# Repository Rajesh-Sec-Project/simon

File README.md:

# simon

------------
Setup
------------

### Step 1

Grab the project's sources using ```git clone https://github.com/Rajesh-Sec-Project/simon.git```.

### Step 2

Build the GUI component, you will need the Qt5 framework properly insstalled alongside with QtMultimedia.
You will also need QtChooser.
Then, type ```cd host && make release```, all should go well and you should see no errors.

### Step 3

Get a drone (and the LED board). Power-on the drone (but don't plut the LEDs board yet).
Connect your computer to the drone's wifi network, then type in ```utils.d/setup.sh```.
Wait some seconds, then plug in the LEDs when requested, the game should start shortly !

------------
Game screenshots
------------

![Main menu]
(https://raw.githubusercontent.com/Rajesh-Sec-Project/simon/master/docs.d/screenshots/main_menu.png)

![High scores hall of fame]
(https://raw.githubusercontent.com/Rajesh-Sec-Project/simon/master/docs.d/screenshots/high_scores.png)

![Settings page]
(https://raw.githubusercontent.com/Rajesh-Sec-Project/simon/master/docs.d/screenshots/settings.png)

------------
Required tools
------------
The project uses the ```make``` build system. It smartly manages the compilation process for the host applications and the cross-compiled applications for the drone.
To build the embedded app, you will need a valid ARM cross-compiler, with its executable in your ```$PATH```.
The host GUI application uses Qt5 and needs its SDK for building.

------------
Build process
------------
When in the root directory, you can run ```make debug``` or ```make release```, depending on your goal. The command will build the drone app, the GUI app and all of their dependencies.
The project contains 2 misc targets, called ```drone-sandbox``` and ```host-sandbox```, which are only present for test purposes. These targets are meant to build an executable, so as no source file are present in their ```src/``` subdirectory, the compilation will fail (stating that no ```main``` function was found). If you want the whole build process to be successful, you will need to add a minimal ```main``` function in the ```drone-sandbox/src``` and ```host-sandbox/src``` directories, for example like this one in a file called ```main.cpp```:

```
int main() {
    return 0;
}
```

If you prefer not to get involved into this, you can only build the individual targets, like ```drone``` or ```host```, just cd into the corresponding directory and run ```make debug``` or ```make release```.

------------
Embedded deployment
------------
If you want to put the application on the drone, run ```cd drone; make push```. This target manages on its own the FTP connection to the drone and the push of the executable.
This assumes that your are on the drone's WiFi network, that its DHCP server has given you an IP and that you can ```ping 192.168.1.1``` without issue.

The ```make push``` command usually takes a few seconds to copy the executable. If it returns immediately, it means that an error occurred (even if none is reported).
If this is happening, it can mean 2 things: either you did not meet the above preconditions, or the ```drone``` command is running (preventing you to overwrite the executable).

Just run the command ```killall -9 program.elf; killall -9 drone``` to terminate the ```drone``` application and turn back in a restartable state. Note that you may want to execute the previous command each time you want to relaunch the ```drone``` application.

The deployment puts the executable in the drone filesystem's ```/data/video/``` directory, and you can run the app by opening a shell on the drone: ```telnet 192.168.1.1```.

------------
Repository structure
------------

Here is a short roadmap of this repository's top-level structure :

* drone         -> The embedded program sources
* drone-sandbox -> An empty playground for embedded programs
* host          -> The host GUI client sources
* host-sandbox  -> An empty playground for host programs
* docs.d        -> Non-source folder for documentation stuff
* gdb.d         -> Script folder for debugging and executable pushing
* hard.d        -> Hardware sources folder
* libs.d        -> Shared libraries (across drone and host) source folder
* mk.d          -> Internal GNU Make scripts for building the project
* utils.d       -> Utilities scripts folder

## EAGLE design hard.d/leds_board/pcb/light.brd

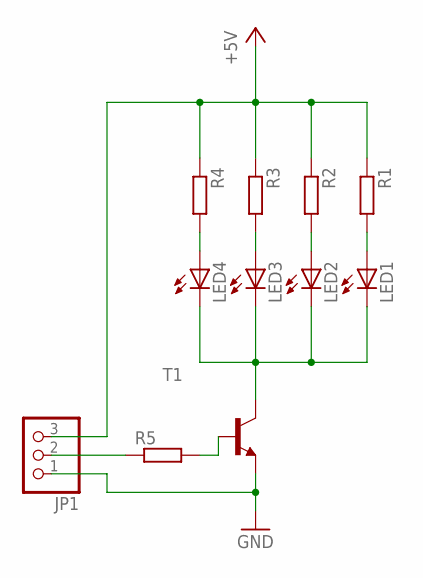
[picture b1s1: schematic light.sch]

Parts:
JP1: PINHD-1X3/90; 1X03/90
LED1, LED2, LED3, LED4: LED3MM
R1, R2, R3, R4, R5: R-EU_0207/10; 0207/10
T1: -NPN-SOT223; SOT223

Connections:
+5V: JP1.3, R1.1, R2.1, R3.1, R4.1
GND: JP1.1, T1.3 (E)
unnamed: LED1.A, R1.2
unnamed: LED2.A, R2.2
unnamed: LED3.A, R3.2
unnamed: LED4.A, R4.2
unnamed: LED1.K (C), LED2.K (C), LED3.K (C), LED4.K (C), T1.4 (C)
unnamed: R5.2, T1.1 (B)
unnamed: JP1.2, R5.1

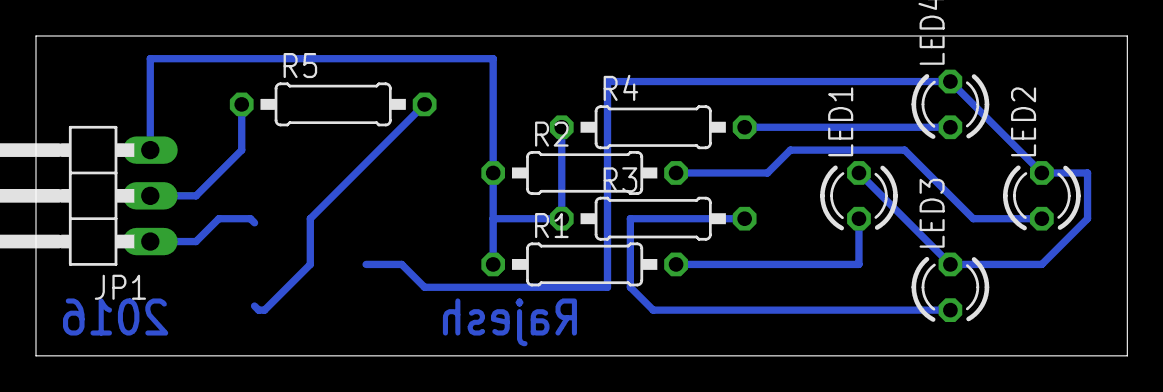
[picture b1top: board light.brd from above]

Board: 2 copper layers, 60.6 x 17.8 mm, 11 parts (1 on the bottom side), 9 nets.

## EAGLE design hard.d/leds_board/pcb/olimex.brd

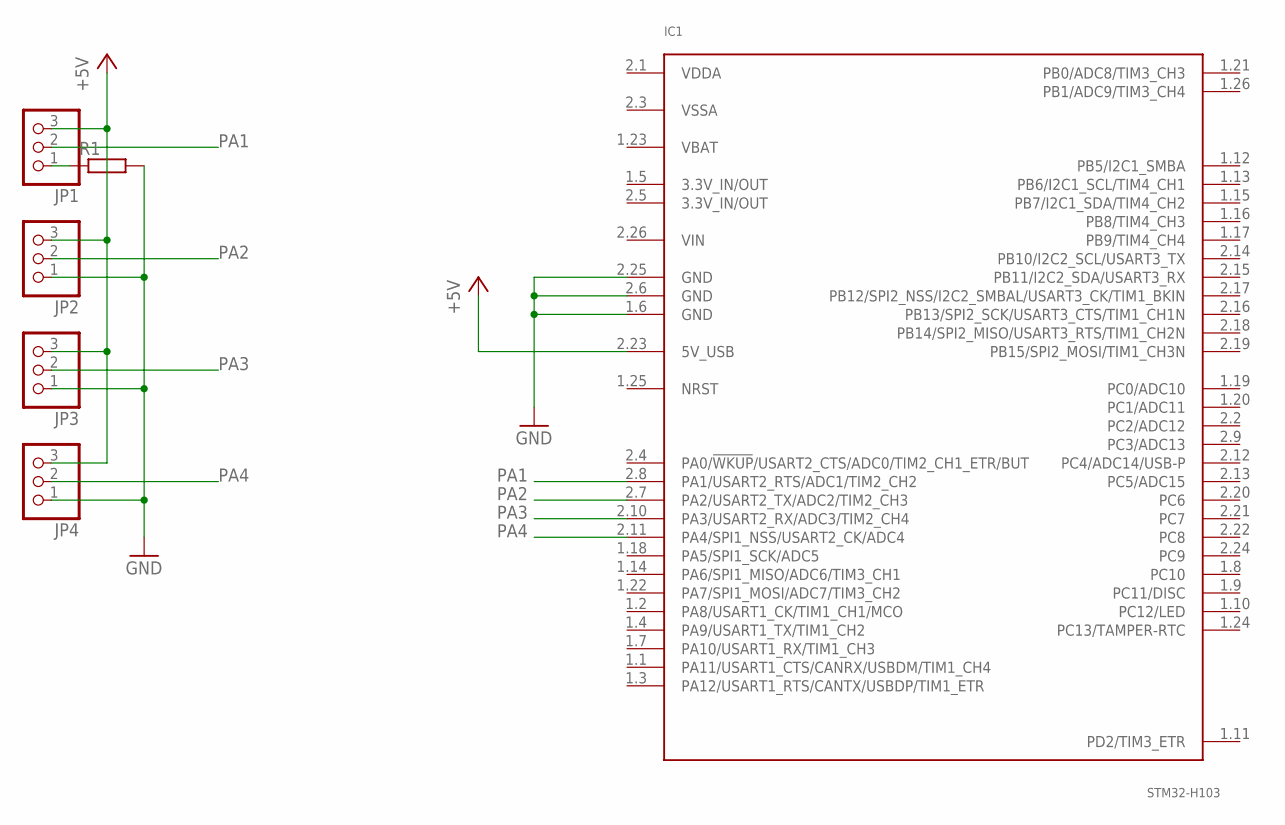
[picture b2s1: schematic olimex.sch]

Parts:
IC1: STM32-H103; OLIMEX_H103_P
JP1, JP2, JP3, JP4: PINHD-1X3/90; 1X03/90
R1: R-EU_0207/10; 0207/10

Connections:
3.3V_IN/OUT: IC1.1.5 (3.3V_IN/OUT), IC1.2.5 (3.3V_IN/OUT)
+5V: IC1.2.23 (5V_USB), JP1.3, JP2.3, JP3.3, JP4.3
GND: IC1.1.6 (GND), IC1.2.6 (GND), IC1.2.25 (GND), JP2.1, JP3.1, JP4.1, R1.2
unnamed: JP1.1, R1.1
PA1: IC1.2.8 (PA1/USART2_RTS/ADC1/TIM2_CH2), JP1.2
PA2: IC1.2.7 (PA2/USART2_TX/ADC2/TIM2_CH3), JP2.2
PA3: IC1.2.10 (PA3/USART2_RX/ADC3/TIM2_CH4), JP3.2
PA4: IC1.2.11 (PA4/SPI1_NSS/USART2_CK/ADC4), JP4.2
VBAT: IC1.1.23 (VBAT)
VDDA: IC1.2.1 (VDDA)
VIN: IC1.2.26 (VIN)
VSSA: IC1.2.3 (VSSA)

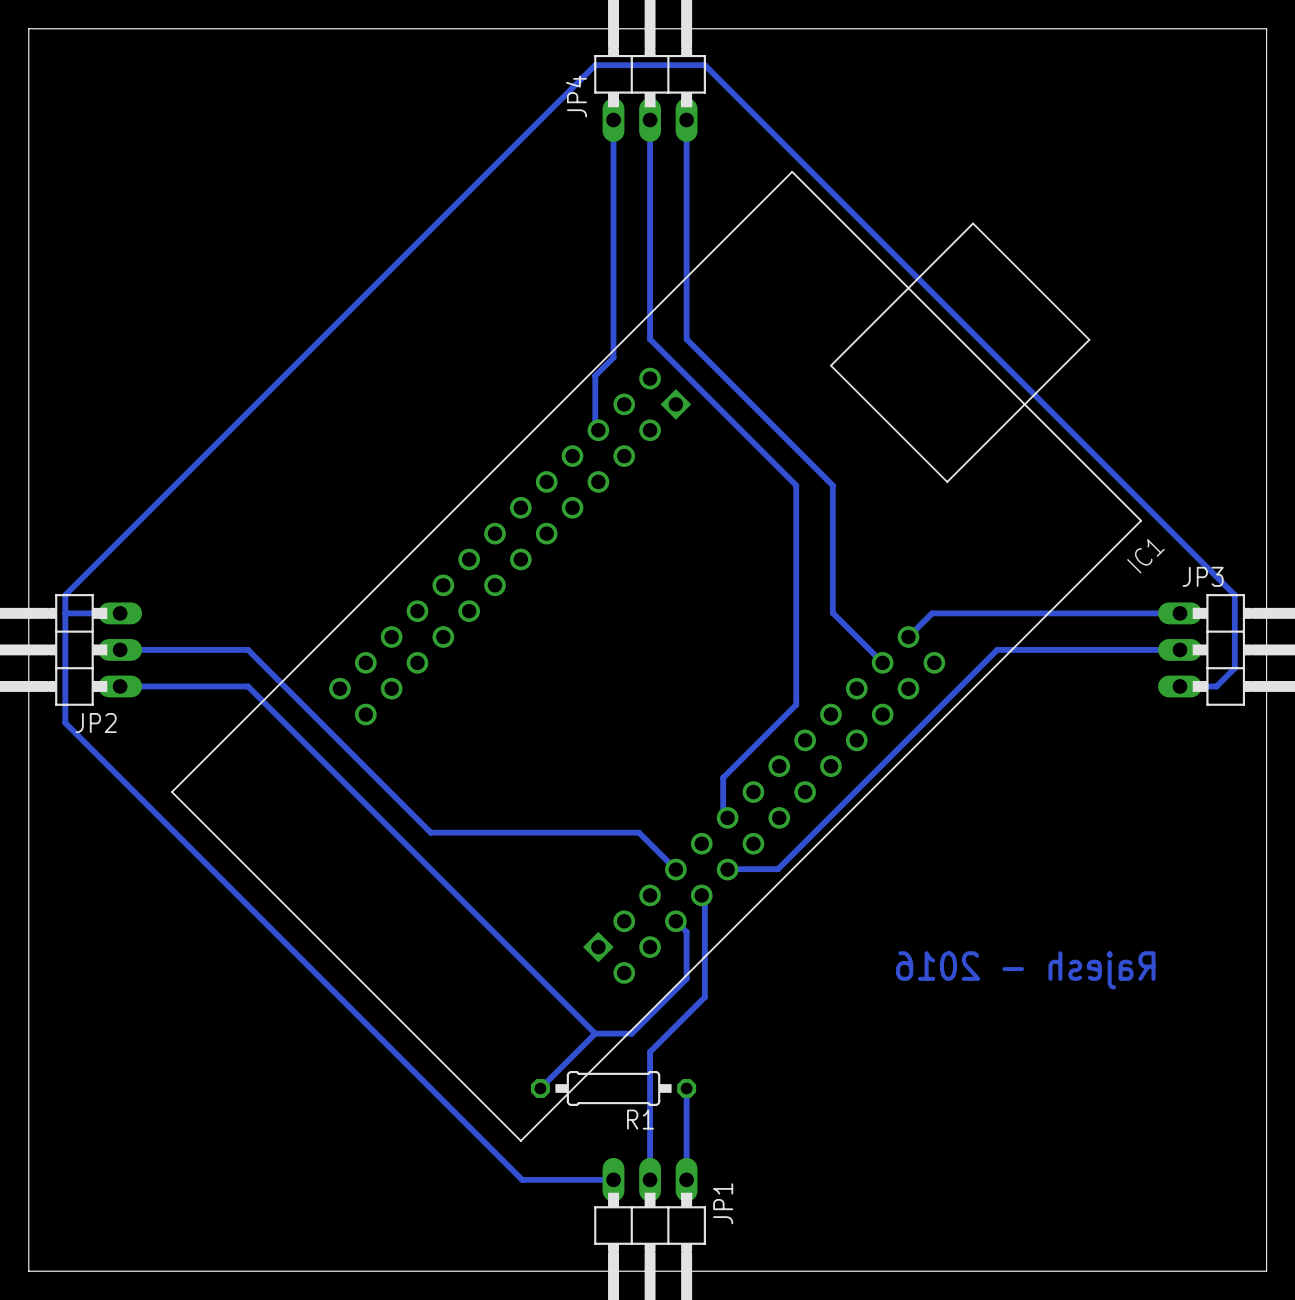
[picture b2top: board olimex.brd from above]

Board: 2 copper layers, 86.0 x 86.3 mm, 6 parts (0 on the bottom side), 8 nets.

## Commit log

2015-11-03 Pushed the build system - Makefile skeletons for embedded and offline source codes - INSTALL.md file for explanation - build system tested good
2015-11-03 Fix typo in INSTALL.md
2015-11-03 Typo fix in INSTALL.md (again !)
2015-11-04 Fixed build system - mk.d/production.mk and mk.d/functions.mk - added static libstdc++ linkage
2015-11-04 Added debug system - see debug/*.sh scripts - can push executable to remote (w/ ftp) - can start/stop debugging session easily - all integrated in the makefiles (push / debug targets)
2015-11-04 Fixed Makefile - two 'debug' rules...
2015-11-04 Modified build & debug system + added shell make target + patched GDB start system (to kill gdbserver before and after session to avoid problems) + updated INSTALL.md
2015-11-05 Fixed push.sh script
2015-11-06 Integrated Qt in the build system - updated INSTALL.md - added help target in Makefiles - added qmake helpers fragments in mk.d/
2015-11-06 Renamed debug/ to gdb.d/ Patched typo in INSTALL.md
2015-11-06 Added a clang-format file, and wrote a small script to automatically format source code
2015-11-06 Configured the Qt project
2015-11-06 Integrated libconf library in project - integrated external dependencies in build system (not yet documented in INSTALL.md)
2015-11-06 Squelette client
2015-11-08 .gitignore
2015-11-08 Formattage
2015-11-08 common
2015-11-08 Added communication protocol bare bones - as an external library in lib.d - added a qemu simulation target (mk.d/qemu.mk)
2015-11-08 Small fixes : - Patched libcomm include guards - Patched external library build system (also override build directory)
2015-11-09 First version of the communication protocol - added BSD socket backends for lcomm::Endpoint - fixed some bugs in lcomm:: - fixed dependency management in build system - fixed root Makefile
2015-11-10 Finishing up libcomm - centralized Packet registerations in a PacketManager static class - added a global lcomm.h header - [ patched .gitignore in libconf submodule ]
2015-11-10 Documented libcomm files - fixed dependency build system (now suports debug/release switch automatically) - added unit tests support for the drone project (make tests-debug or tests-release)
2015-11-10 Fixed .gitignore
2015-11-10 Patched .clang-format file - for compat. with clang 3.5 (very lightweigth) - to bind pointers to types (i didn't touched braces Rémi :) ) - to break initializers in constructors
2015-11-10 Added a host-sandbox project for quick integration tests - fixed project names in */conf.mk to reflect their parent folder names
2015-11-10 Formatted previous commits (sorry for dup commit) - added host-sandbox folder to utils.d/format.sh
2015-11-13 Added notes file plus some at and navdata headers
2015-11-13 Fixed makefiles
2015-11-13 Simplified Endpoints and Socket interactions
2015-11-13 Fixed tests
2015-11-13 Added UI's gamepad bare bones - plus gamepad packet
2015-11-13 More GUI stuff
2015-11-13 drone-sandbox
2015-11-13 libcontrol
2015-11-13 More gamepad stuff
2015-11-13 emma, control
2015-11-13 Fixed Q_OBJECT missing
2015-11-13 Added a general info packet in libcomm
2015-11-13 Added new enums to GamepadPacket (land and take off)
2015-11-13 Game system, take off and landing
2015-11-13 Patched game system (less threads :()
2015-11-13 Formating script is up to date.
2015-11-13 Formatted source code
2015-11-14 Better interface to libcontrol
2015-11-14 Endpoint subscriber is now taken by reference
2015-11-14 Endpoint::write
2015-11-14 Subscriber::notify
2015-11-14 Specified the thread-safety of the Socket::read and Socket::write methods
2015-11-14 Cleaned the ServerSocket class from dynamic allocations
2015-11-14 Finished libcomm trimming
2015-11-14 Removed old code from GameSystem, added -Wall flags to the compiler
2015-11-14 Added override specifier where appropriate
2015-11-14 Formatting
2015-11-16 Fixed regression in makefile: missing static libstdc++ in the drone program
2015-11-16 Turned off AT command logging (logging is now on demand).
2015-11-16 Better logging of user actions in the host's application.
2015-11-16 The embedded app is now easier to terminate.
2015-11-16 Small refactoring of the host app.
2015-11-16 Hardenned the connection between the drone and the host: a lost or nonexisting connection provokes reconnection attempts.
2015-11-19 Added a script to start the game on the drone
2015-11-19 Reducing the per-thread stack sie allows more threads to be spawned; thus the game loop thread has been added again.
2015-11-19 libcontrol has now a blocking connection initialization
2015-11-19 Added an UDP spoofing class in libcomm (for navdata)
2015-11-20 Improved drone control's app launch script
2015-11-20 Removed read threads from ClientSocket and ServerSocket
2015-11-20 Removed unnecessary mutex
2015-11-20 Navdata driver working ! - now using libpcap to sniff traffic initiated by spoofer
2015-11-21 add of Moves and RandomSequence
2015-11-22 Added NavdataController (based on spoofing + sniffing) - not yet tested on drone
2015-11-23 Added final (and working !) navdata controller - changed the main game loop structure (and addex watchdog management) - renamed some file lowercase - fixed the lcontrol lib (watchdog fix, added comma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
2015-11-23 Added tag detection bare bones (conf problems !!) - did some renaming of files
2015-11-23 Oops!
2015-11-24 Small changes to drone/
2015-11-24 Added logging system base (not yet tested on the drone) - added a GameElement class to provide global GameSystem access for logging - added a lcomm::LogPacket class (w/ 4 levels of logging, trace/mes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
2015-11-25 Added log interface + information packets (for the UI to know the drone's state) - fixed a LOT (really, A LOOOT) of bugs in the communication things - /!\ PLEASE DON'T TOUCH IT ANYMORE /!\ - added a 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
2015-11-26 Updated game sequence
2015-11-26 Small changes
2015-11-26 Local logging level
2015-11-26 Preliminary drone position control interface
2015-11-26 Added a clock to the game system
2015-11-27 Removed test values
2015-11-27 TAG DETECTION WORKING YOUHOUUUUUUUU - Added multiconfiguration support
2015-11-27 Fixed the game system's clock wraparound, and fixed the game loop's per-iteration wait
2015-11-27 Added tag detetion support in the GUI
2015-11-27 Minimal log level for the GUI
2015-11-27 Main
2015-11-27 Removed the random sequence's test
2015-11-27 Removed unused NAT documentation
2015-11-28 Added compilation/deployment instructions in the README.md file
2015-11-28 Code that compiles is somewhat better, I guess
2015-11-28 gamepad subscriber + gamesystem add of error recognition
2015-11-28 Previous errors modified
2015-11-28 Added a gamepad to control the drone's position
2015-11-28 position control update
2015-11-28 add print sequence
2015-11-28 change debug game system
2015-11-28 debug gamesystem
2015-11-30 change move recognition
2015-11-30 Removed test files
2015-11-30 Integrated Emma's work
2015-11-30 Better GUI, factorization of some code
2015-11-30 Removed empty sources
2015-11-30 Added a black ring aroung the tag target
2015-11-30 Rename RoundelController
2015-12-01 Removed some warnings related to bad aliasing
2015-12-01 Added sprint 0 and 2's review document
2015-12-01 Added tag position conversion (to cm) - started detection compensation
2015-12-01 Added an explanation about tag detection calibration (in docs.d)
2015-12-03 Position control updated avec control selon altitude
2015-12-03 Added a game GUI
2015-12-03 T53 integrated the game control onto the drone
2015-12-03 T53 integrated the host with the client
2015-12-08 Added user move detection algorithms [T54] - added matlab design script and data - all implemented in tagcontroller.h/cpp
2015-12-08 New update on PID and position control T23
2015-12-08 Bug fix in libcontrol
2015-12-08 More work on the PID
2015-12-11 Tuned euler angles PID Added basic moves eecution
2015-12-12 Removed PID samples from repo
2015-12-12 libcontrol is now thread-safe
2015-12-12 T20 T24 Added a position control thread that executes atomic movements.
2015-12-12 Removed the stop button from the gamepads
2015-12-12 T44 Updated motion algorithm
2015-12-12 add of score counting T40 and score display T41
2015-12-17 Changed files mode, don't know why the x bit was set on them.
2015-12-17 PID tuning
2016-01-04 Added a GUI mock for the game, and attributed roles to the developers.
2016-01-07 interface compile pas
2016-01-07 Updated ViewManager and disconnect from the drone
2016-01-10 score: display and save
2016-01-10 Added LED board schematics and first driver version on drone side
2016-01-11 LEDs board driver OK - added driver module 'cdc-acm.ko' in docs.d - be careful to insmod it at startup
2016-01-12 Fixed UI switching
2016-01-12 GameOver message and overall game integration
2016-01-12 Added sprint review presentations 3 and 4.
2016-01-12 Fixes
2016-01-14 Created a skin for the game - added some fonts - changed layouts - TODO: - display tag position in gameview - fix pause/resume bug - fix score bug
2016-01-18 Integrated LED display to the game - added win/lose animations - added user input feedback through LEDs and GUI
2016-01-18 - fixed main menu at startup
2016-01-18 score marche
2016-01-18 Added a sound manager and contextual music backgrounds.
2016-01-18 Added sound notification packet
2016-01-18 Added a sound notification packet (correction)
2016-01-18 Added sound to Qt ressources file
2016-01-18 Updated music locations
2016-01-18 Added sound effects
2016-01-21 Fixed start message sent to drone + Qt5 issues
2016-01-21 The generated moves sequence should now have a uniform distribution.
2016-01-21 Added delay before starting the game
2016-01-21 Loading screen
2016-01-21 Renamed gameview to GameView
2016-01-21 Added the credits view
2016-01-21 Added a library for the chrono stuff.
2016-01-21 Added settings
2016-01-21 Fixed the score updating rate.
2016-01-21 Fixed settings
2016-01-21 Disables music when requested.
2016-01-21 Formatting.
2016-01-21 Patched high score system to use QSettings instead of file
2016-01-21 Scores
2016-01-26 Added Sprint review 5
2016-01-26 Added licence headers to source files.
2016-01-26 Added LEDs board embedded source code (not cleaned yet)
2016-01-26 Added license to relevant files in leds_board/soft
2016-01-26 Updated README.md + added screenshots
2016-01-27 Added setup script plus readymade drone binary
